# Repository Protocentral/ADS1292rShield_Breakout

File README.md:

ProtoCentral ADS1292R ECG/respiration shield and breakout board 
================================

[  
Dont have it yet? But one here: ADS1292R ECG/Respiration Shield for Arduino- v2 (PC-4128)](https://protocentral.com/product/ads1292r-ecg-respiration-shield-for-arduino-v2/)

[  
Dont have it yet? But one here: ADS1292R ECG/Respiration Breakout for Arduino- v3 (PC-4116)](https://protocentral.com/product/ads1292r-ecg-respiration-breakout-kit/)

The Arduino library for this product is now available in the **[ProtoCentral ADS1292R Arduino Library repo](https://github.com/Protocentral/protocentral-ads1292r-arduino)**

**Breakout v4:** KiCad design files and the schematic PDF are in [`hardware/breakout/v4`](hardware/breakout/v4). v4 has a new 10-pin host header (CS, MOSI, SCK, MISO, DRDY, START, RST, CLK, VCC, GND) with the ADS1292R clock brought out, so the pinout below applies to v3 only. Earlier revisions remain in `hardware/breakout` and `hardware/shield`.

Easily monitor ECG and respiration using your Arduino with this plug-in shield. The version 2 of this product adds a new SPI pin header making it compatible with newer Arduino devices including the Arduino Yun and 3.5mm connector for the electrodes. We now include the electrodes and cable also with the shield

Just plug it into an Arduino and you're ready to go. The 3.5 mm circular connector provides an easy way to connect electodes to the shield. The other end of this cable has snaps for standard ECG electrodes. We also include a pakc of 10 disposable EG electrodes. It accepts two ECG electrodes and one Driven Right Leg (DRL) electrode for common mode noise reduction. 

Another interesting feature of this shield is that you can also measure the respiratory activity using the same two electrodes connected to the shield. The ADS1292R uses a method known as impedance pneumography to measure respiration using the changes in chest impedance caused during respiration. 

Features:
----------
* ADS1292R Analog Front End IC
* Onboard 3.3V voltage regulator for low noise
* Onboard logic level transalators for Arduino interface
* Prototyping area for adding addtional components

Includes:
----------
* ADS1292R Arduino shield
* Electrode cable with 3.5mm connector and ECG electrodes connectors
* Pack of 10 disposable stick-on ECG electrodes.

Connecting the shield to your Arduino
-------------------------------------
Connect the ECG/Respiration shield to the Arduino by stacking it on top of your Arduino. This shield uses the SPI interface  to communicate with the Arduino. Since this includes the ICSP header, which is used on newer Arduinos for SPI communication,  this shield is also compatible newer Arduino boards such as the Arduino Yun and Due.
 
Wiring the Breakout to your Arduino
------------------------------------
 If you have bought the breakout the connection with the Arduino board is as follows:
 
|ads1292r pin label| Arduino Connection   |Pin Function      |
|----------------- |:--------------------:|-----------------:|
| VDD              | +5V                  |  Supply voltage  |             
| PWDN/RESET       | D4                   |  Reset           |
| START            | D5                   |  Start Input     |
| DRDY             | D6                   |  Data Ready Outpt|
| CS               | D7                   |  Chip Select     |
| MOSI             | D11                  |  Slave In        |
| MISO             | D12                  |  Slave Out       |
| SCK              | D13                  |  Serial Clock    |
| GND              | Gnd                  |  Gnd             |
 
Installing the Arduino libraries 
---------------------------------
Arduino library for this boards is now available at https://github.com/Protocentral/protocentral-ads1292r-arduino or from the Arduino Library Manager inside the Arduino IDe. 

If you have correctly installed the libraries, the example sketeches should now be available from within Arduino at File-->Examples-->ProtoCentral ADS1292R library.

Using the ProtoCentral OpenView GUI
-----------------------------------

The GUI for visualizing the ECG and Respiration as well as parameters like Heart rate and Respiration rate is written in Processing, based on Java and is cross-compilable across platforms. 
 
Java 8 is required on all platforms for running the processing-based GUI application. You can download Java for your platform from the [Official Java website](https://java.com/en/download/).

You can download and install [ProtoCentral OpenView](https://github.com/Protocentral/protocentral_openview) from here: https://github.com/Protocentral/protocentral_openview

Connecting the ECG Electrodes
------------------------------
 A 3-electrode cable along with a standard stereo jack is provided along with the shield to connect the electrodes to the     shield. The electrode input connector is highlighted in the below picture.
 
 The other side of the electrode connector would connect to snap-on electrodes attached to the body. For testing purposes,    you can use an ECG simulator to provide inputs to the board. 

 Warning:
 When connecting the electodes to the body, it is safer to disconnect the mains power source to the Arduino. For example, if  you are using the Arduino along with a laptop, disconnecting the battery charger from the laptop would be a safe option.
 
Placing the Electrodes on the body
---------------------------------

License Information
===================
This product is open source! 

Both, our hardware and software are open source and licensed under the following licenses:

Hardware
---------

**All hardware is released under the [CERN-OHL-P v2](https://ohwr.org/cern_ohl_p_v2.txt)** license.

Copyright CERN 2020.

This source describes Open Hardware and is licensed under the CERN-OHL-P v2.

You may redistribute and modify this documentation and make products
using it under the terms of the CERN-OHL-P v2 (https:/cern.ch/cern-ohl).
This documentation is distributed WITHOUT ANY EXPRESS OR IMPLIED
WARRANTY, INCLUDING OF MERCHANTABILITY, SATISFACTORY QUALITY
AND FITNESS FOR A PARTICULAR PURPOSE. Please see the CERN-OHL-P v2
for applicable conditions

Software
--------

**All software is released under the MIT License(http://opensource.org/licenses/MIT).**

THE SOFTWARE IS PROVIDED "AS IS", WITHOUT WARRANTY OF ANY KIND, EXPRESS OR IMPLIED, INCLUDING BUT NOT LIMITED TO THE WARRANTIES OF MERCHANTABILITY, FITNESS FOR A PARTICULAR PURPOSE AND NONINFRINGEMENT. IN NO EVENT SHALL THE AUTHORS OR COPYRIGHT HOLDERS BE LIABLE FOR ANY CLAIM, DAMAGES OR OTHER LIABILITY, WHETHER IN AN ACTION OF CONTRACT, TORT OR OTHERWISE, ARISING FROM, OUT OF OR IN CONNECTION WITH THE SOFTWARE OR THE USE OR OTHER DEALINGS IN THE SOFTWARE.

Documentation
-------------
**All documentation is released under [Creative Commons Share-alike 4.0 International](http://creativecommons.org/licenses/by-sa/4.0/).**

You are free to:

* Share — copy and redistribute the material in any medium or format
* Adapt — remix, transform, and build upon the material for any purpose, even commercially.
The licensor cannot revoke these freedoms as long as you follow the license terms.

Under the following terms:

* Attribution — You must give appropriate credit, provide a link to the license, and indicate if changes were made. You may do so in any reasonable manner, but not in any way that suggests the licensor endorses you or your use.
* ShareAlike — If you remix, transform, or build upon the material, you must distribute your contributions under the same license as the original.

Please check [*LICENSE.md*](LICENSE.md) for detailed license descriptions.

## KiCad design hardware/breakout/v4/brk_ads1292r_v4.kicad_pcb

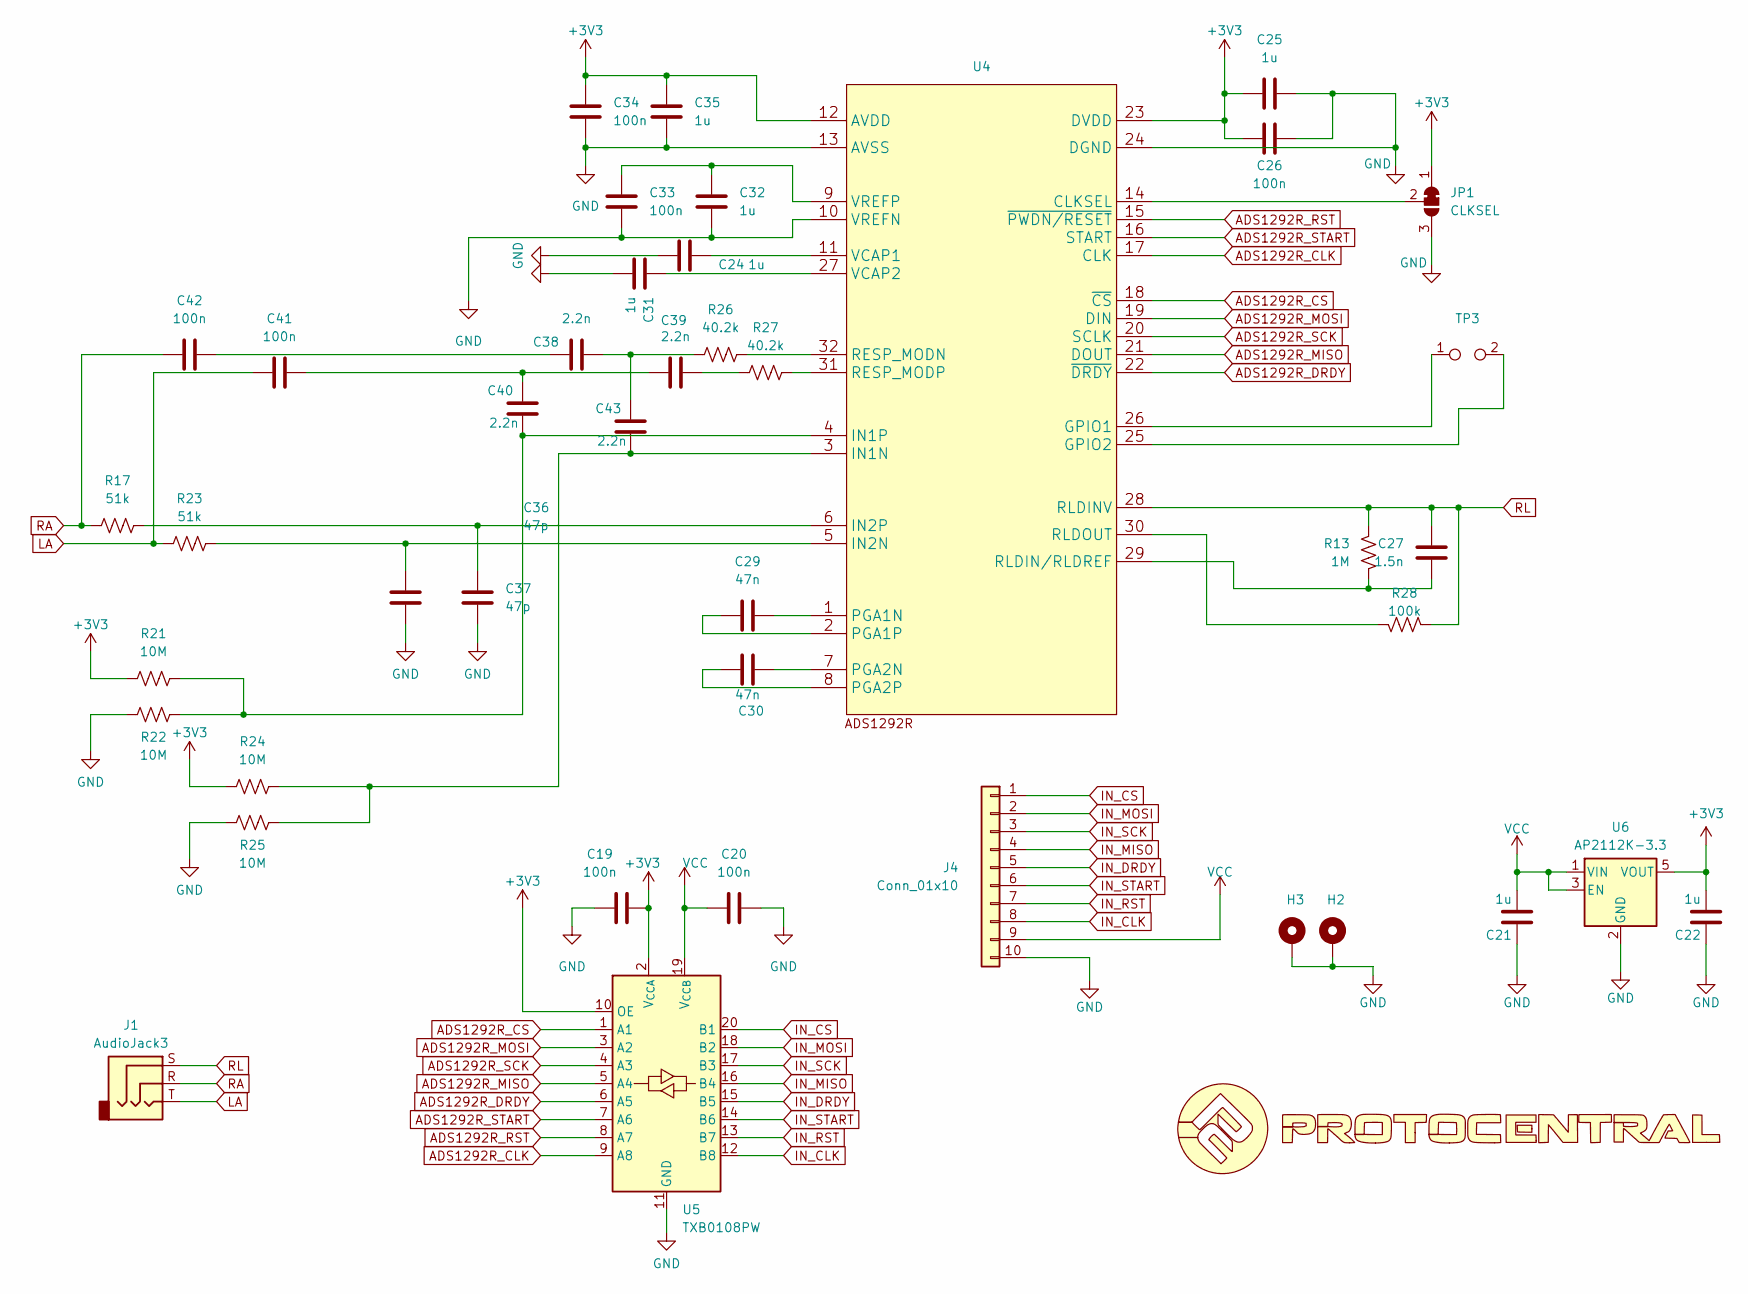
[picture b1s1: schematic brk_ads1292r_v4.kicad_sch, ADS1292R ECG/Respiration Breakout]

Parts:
C19, C20, C26, C33, C34, C41, C42: 100n; C_0402_1005Metric
C21, C22, C24, C25, C31, C32, C35: 1u; C_0402_1005Metric
C27: 1.5n; C_0402_1005Metric
C29, C30: 47n; C_0402_1005Metric
C36, C37: 47p; C_0402_1005Metric
C38, C39, C40, C43: 2.2n; C_0402_1005Metric
H2, H3: MountingHole_Pad; MountingHole_2.2mm_M2_DIN965_Pad_TopBottom
J1: AudioJack3; Jack_3.5mm_CUI_SJ-3523-SMT_Horizontal
J4: Conn_01x10; PinSocket_1x10_P2.54mm_Vertical
JP1: CLKSEL; SolderJumper-3_P1.3mm_Bridged2Bar12_RoundedPad1.0x1.5mm
R13: 1M; R_0402_1005Metric
R17, R23: 51k; R_0402_1005Metric
R21, R22, R24, R25: 10M; R_0402_1005Metric
R26, R27: 40.2k; R_0402_1005Metric
R28: 100k; R_0402_1005Metric
TP3: TestPoint_2Pole; TestPoint_2Pads_Pitch2.54mm_Drill0.8mm
U1: LOGO
U4: ADS1292R; PBS32
U5: TXB0108PW; TSSOP-20_4.4x6.5mm_P0.65mm
U6: AP2112K-3.3; SOT-23-5

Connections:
+3V3: C19.1, C22.2, C25.2, C26.2, C34.1, C35.1, JP1.1 (A), R21.1, R24.1, U4.12 (AVDD), U4.23 (DVDD), U5.2 (V_{CCA}), U5.10 (OE), U6.5 (VOUT)
ADS1292R_CLK: U4.17 (CLK), U5.9 (A8)
ADS1292R_CS: U4.18 (~CS), U5.1 (A1)
ADS1292R_DRDY: U4.22 (~DRDY), U5.6 (A5)
ADS1292R_MISO: U4.21 (DOUT), U5.5 (A4)
ADS1292R_MOSI: U4.19 (DIN), U5.3 (A2)
ADS1292R_RST: U4.15 (~PWDN/RESET), U5.8 (A7)
ADS1292R_SCK: U4.20 (SCLK), U5.4 (A3)
ADS1292R_START: U4.16 (START), U5.7 (A6)
GND: C19.2, C20.2, C21.1, C22.1, C24.2, C25.1, C26.1, C31.1, C32.2, C33.2, C34.2, C35.2, C36.2, C37.2, H2.1 (1_1), H3.1 (1_1), J4.10, JP1.3 (B), R22.1, R25.1, U4.10 (VREFN), U4.13 (AVSS), U4.24 (DGND), U5.11 (GND), U6.2 (GND)
IN_CLK: J4.8, U5.12 (B8)
IN_CS: J4.1, U5.20 (B1)
IN_DRDY: J4.5, U5.15 (B5)
IN_MISO: J4.4, U5.16 (B4)
IN_MOSI: J4.2, U5.18 (B2)
IN_RST: J4.7, U5.13 (B7)
IN_SCK: J4.3, U5.17 (B3)
IN_START: J4.6, U5.14 (B6)
LA: C41.2, J1.T, R23.1
unnamed: C38.1, C43.1, R26.1
unnamed: C38.2, C42.1
unnamed: C39.1, R27.1
unnamed: C39.2, C40.1, C41.1
unnamed: JP1.2 (C), U4.14 (CLKSEL)
unnamed: TP3.1, U4.26 (GPIO1)
unnamed: TP3.2, U4.25 (GPIO2)
unnamed: C43.2, R24.2, R25.2, U4.3 (IN1N)
unnamed: C40.2, R21.2, R22.2, U4.4 (IN1P)
unnamed: C36.1, R23.2, U4.5 (IN2N)
unnamed: C37.1, R17.2, U4.6 (IN2P)
unnamed: C29.1, U4.1 (PGA1N)
unnamed: C29.2, U4.2 (PGA1P)
unnamed: C30.1, U4.7 (PGA2N)
unnamed: C30.2, U4.8 (PGA2P)
unnamed: R26.2, U4.32 (RESP_MODN)
unnamed: R27.2, U4.31 (RESP_MODP)
unnamed: C27.1, R13.2, U4.29 (RLDIN/RLDREF)
unnamed: R28.2, U4.30 (RLDOUT)
unnamed: C24.1, U4.11 (VCAP1)
unnamed: C31.2, U4.27 (VCAP2)
unnamed: C32.1, C33.1, U4.9 (VREFP)
RA: C42.2, J1.R, R17.1
RL: C27.2, J1.S, R13.1, R28.1, U4.28 (RLDINV)
VCC: C20.1, C21.2, J4.9, U5.19 (V_{CCB}), U6.1 (VIN), U6.3 (EN)

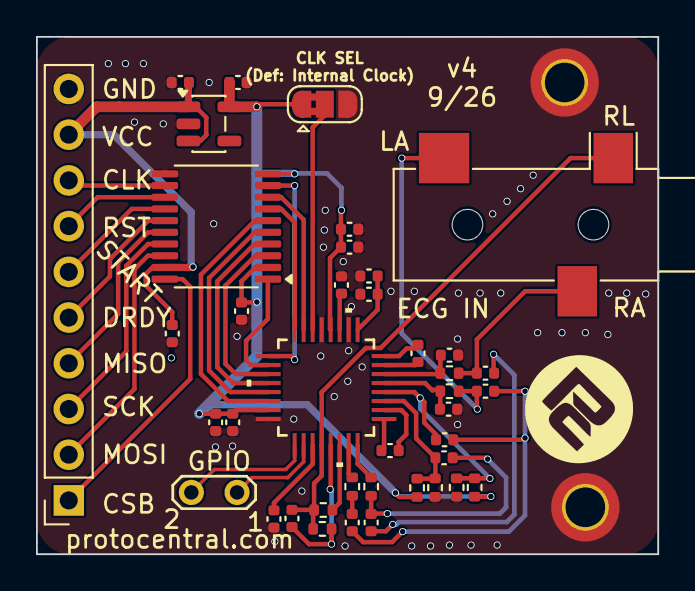
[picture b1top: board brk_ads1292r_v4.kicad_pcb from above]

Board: 2 copper layers, 34.5 x 28.7 mm, 42 parts (0 on the bottom side), 44 nets.

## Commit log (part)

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2015-10-06 :tada: Added .gitattributes & .gitignore files
2015-10-06 ECGShield/breakout
2015-10-22 Design File
2015-10-22 datasheet
2015-10-30 Brainbay setup and config file
2016-05-18 Included Processing Sketch for ADS1292rShield_Breakout
2016-05-18 Removed Processing
2016-05-18 Processing Libraries
2016-05-18 Processing Sketch
2016-06-15 added arduino processing sketch
2016-06-16 Final Output
2016-06-16 Updated Libraries
2016-07-02 Libraries
2016-08-23 Added processing sketch for Arduino
2016-10-14 Processing Code
2016-10-14 Arduino Library
2016-11-18 Added license information
2016-11-18 Updated License information
2016-12-01 added new design file
2017-02-20 updated sketch
2017-02-20 updated skecth
2017-03-20 Changed folder structure with new updated GUI
2017-03-20 updated the links, and images
2017-03-20 Updated license information in Readme
2017-04-13 updated image
2017-04-21 Added Kalam32 example code
2017-04-22 Added GUI for Kalam32 TCP client
2017-04-25 Added mDNS Support
2017-04-25 Updated TCP GUI to support Kalam32 mDNS
2017-06-29 added design pdf file for v3 breakout
2017-06-30 added design file for v3
2017-08-22 Added Heart rate algorithm
    Added filter function, Heart rate calculation.
2020-10-21 Update README.md
    Edited Readme file
2020-10-25 Replaced images and links in README.md
2020-10-30 reorganised
2020-10-30 fixed indentation
2020-10-31 disabled algos for respiration
2020-12-31 Removed existing GUI and Arduino library (moved)
2020-12-31 Renamed hardware folder
2021-03-26 Updated License

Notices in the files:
README.md:
CC-BY-SA-4.0
